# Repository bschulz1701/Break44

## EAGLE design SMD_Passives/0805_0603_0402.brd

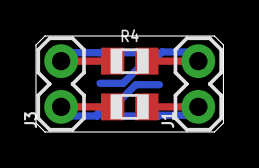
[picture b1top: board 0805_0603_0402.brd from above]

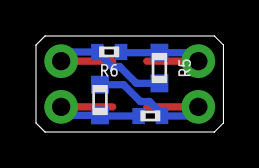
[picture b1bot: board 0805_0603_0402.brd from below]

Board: 2 copper layers, 10.4 x 5.3 mm, 8 parts (4 on the bottom side), 4 nets.

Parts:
J1, J3: 1X02
R1, R4: R0805
R2, R5: R0603
R3, R6: R0402

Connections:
R1_A: J3.1, R1.1, R2.1, R3.1
R1_B: J1.1, R1.2, R2.2, R3.2
R2_A: J3.2, R4.1, R5.1, R6.1
R2_B: J1.2, R4.2, R5.2, R6.2

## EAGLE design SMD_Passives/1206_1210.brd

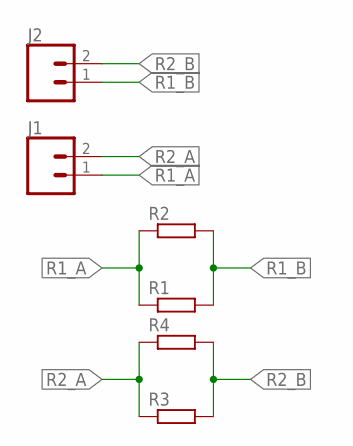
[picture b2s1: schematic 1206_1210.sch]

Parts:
J1, J2: CONN_02; 1X02
R1, R3: R-EU_R1210; R1210
R2, R4: R-EU_R1206; R1206

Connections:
R1_A: J1.1, R1.1, R2.1
R1_B: J2.1, R1.2, R2.2
R2_A: J1.2, R3.1, R4.1
R2_B: J2.2, R3.2, R4.2

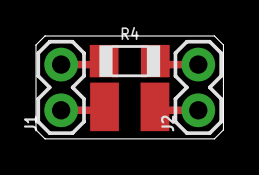
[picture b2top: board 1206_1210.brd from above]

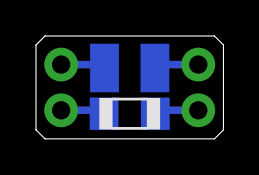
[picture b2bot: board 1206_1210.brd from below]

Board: 2 copper layers, 10.4 x 5.7 mm, 6 parts (2 on the bottom side), 4 nets.

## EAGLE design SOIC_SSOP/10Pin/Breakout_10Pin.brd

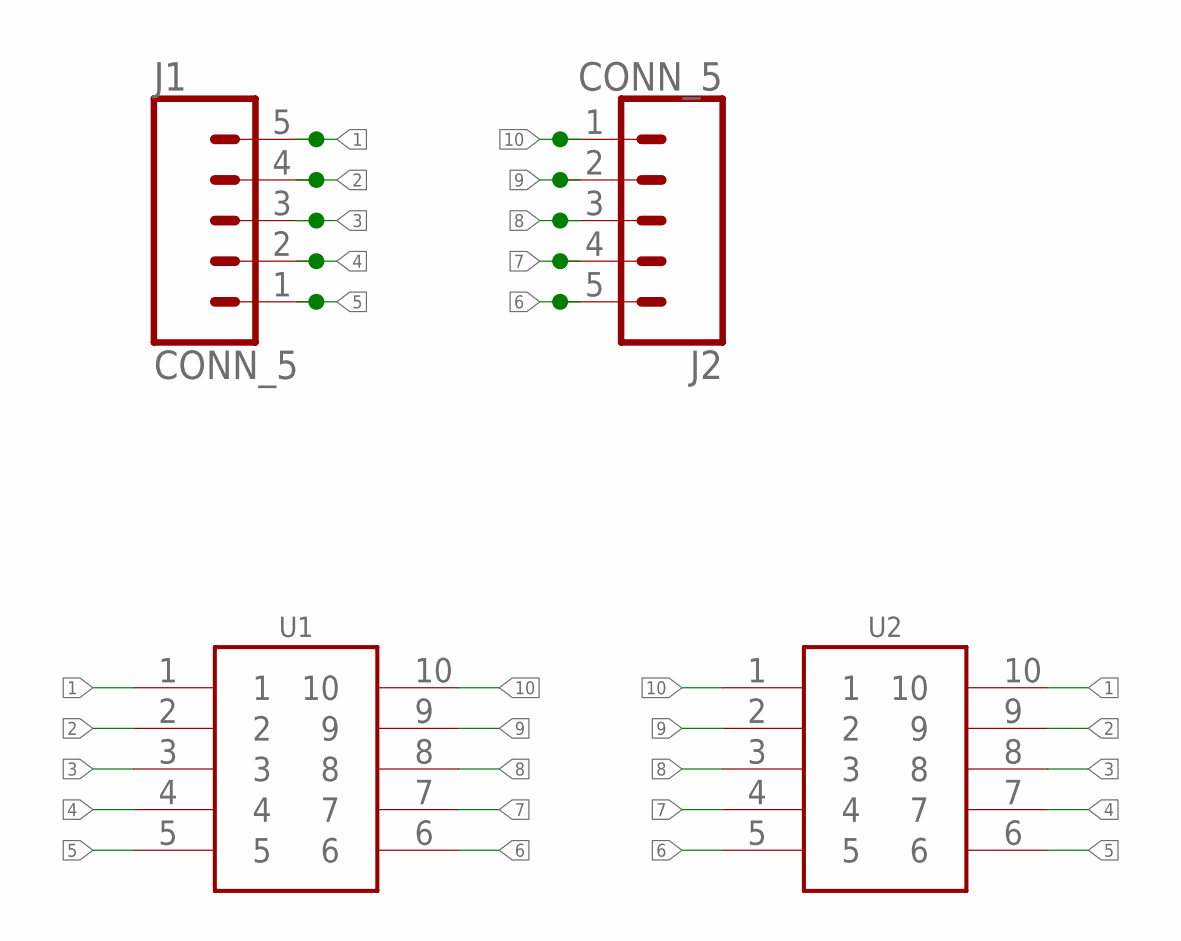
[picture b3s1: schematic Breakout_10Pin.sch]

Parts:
J1, J2: CONN_5; 1X05
U1: GEN_10SOIC10; SO10
U2: GEN_10VSSOP10; VSSOP_10

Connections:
1: J1.5, U1.1, U2.10
2: J1.4, U1.2, U2.9
3: J1.3, U1.3, U2.8
4: J1.2, U1.4, U2.7
5: J1.1, U1.5, U2.6
6: J2.5, U1.6, U2.5
7: J2.4, U1.7, U2.4
8: J2.3, U1.8, U2.3
9: J2.2, U1.9, U2.2
10: J2.1, U1.10, U2.1

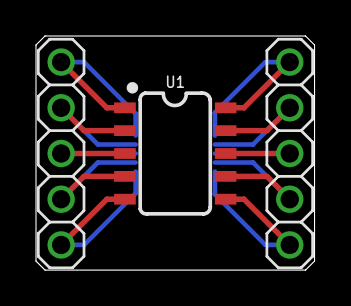
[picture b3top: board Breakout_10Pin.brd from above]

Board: 2 copper layers, 15.5 x 13.0 mm, 4 parts (1 on the bottom side), 10 nets.

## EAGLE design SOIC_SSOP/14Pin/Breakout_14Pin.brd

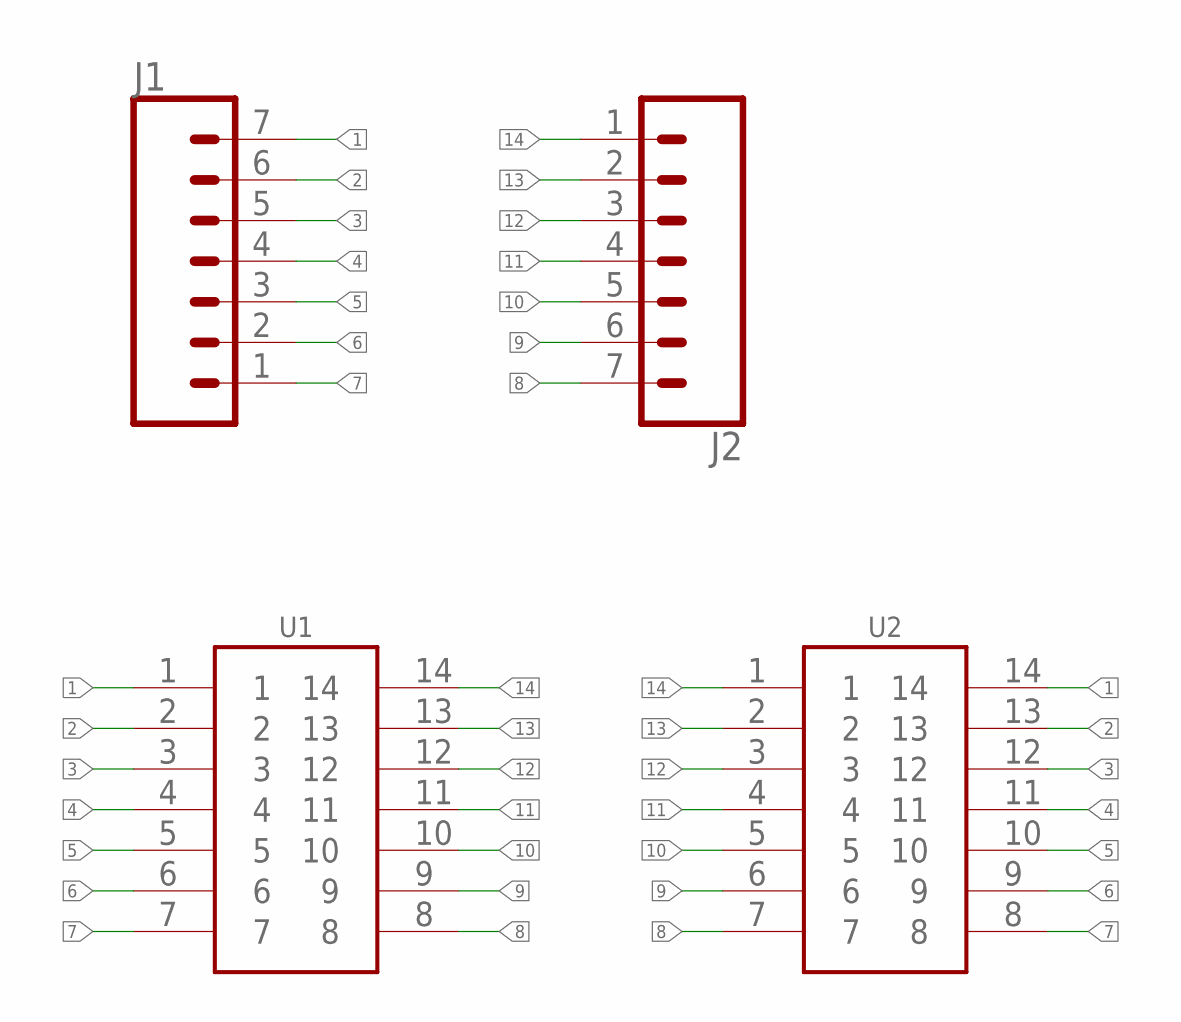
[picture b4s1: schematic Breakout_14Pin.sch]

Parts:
J1, J2: CONN_07; 1X07
U1: GEN_14SOIC; SO14
U2: GEN_14TSSOP; TSSOP14

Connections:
1: J1.7, U1.1, U2.14
2: J1.6, U1.2, U2.13
3: J1.5, U1.3, U2.12
4: J1.4, U1.4, U2.11
5: J1.3, U1.5, U2.10
6: J1.2, U1.6, U2.9
7: J1.1, U1.7, U2.8
8: J2.7, U1.8, U2.7
9: J2.6, U1.9, U2.6
10: J2.5, U1.10, U2.5
11: J2.4, U1.11, U2.4
12: J2.3, U1.12, U2.3
13: J2.2, U1.13, U2.2
14: J2.1, U1.14, U2.1

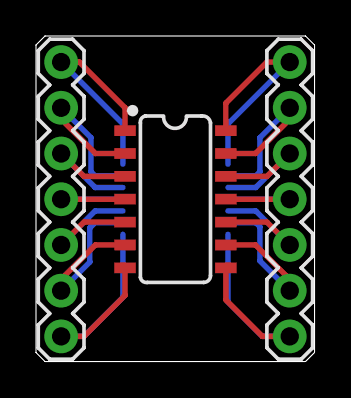
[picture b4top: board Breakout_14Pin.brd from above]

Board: 2 copper layers, 15.5 x 18.1 mm, 4 parts (1 on the bottom side), 14 nets.

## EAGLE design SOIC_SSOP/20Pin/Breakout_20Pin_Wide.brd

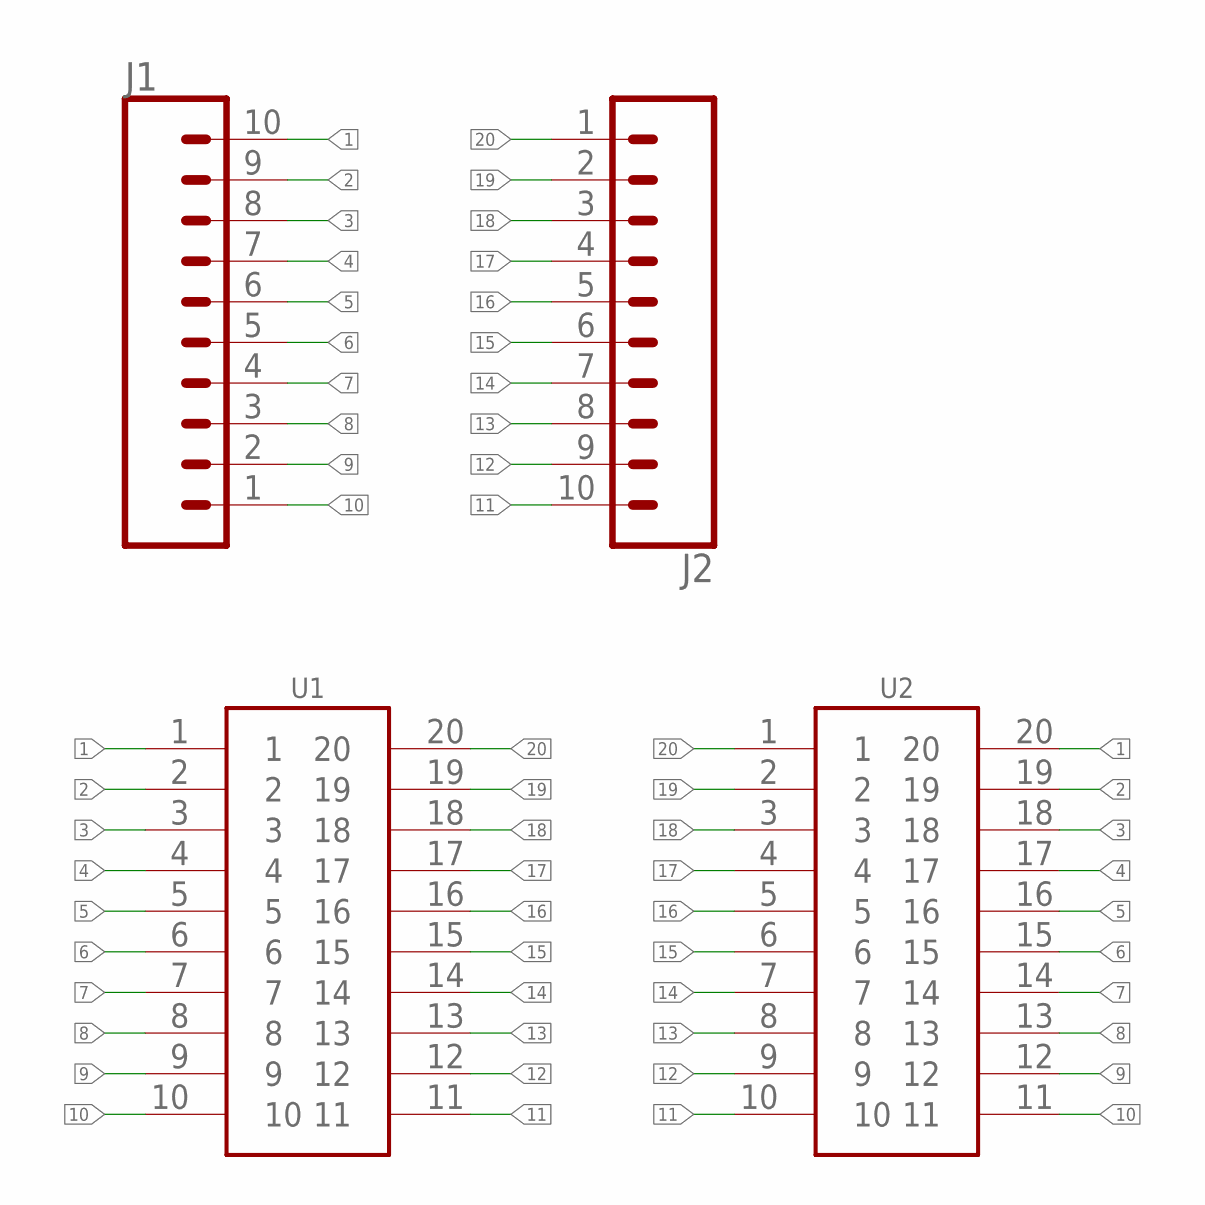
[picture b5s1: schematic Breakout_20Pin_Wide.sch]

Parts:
J1, J2: CONN_10"; 1X10
U1: GEN_20SOIC_W; SO-20DW
U2: GEN_20SSOP; SSOP20

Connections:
1: J1.10, U1.1, U2.20
2: J1.9, U1.2, U2.19
3: J1.8, U1.3, U2.18
4: J1.7, U1.4, U2.17
5: J1.6, U1.5, U2.16
6: J1.5, U1.6, U2.15
7: J1.4, U1.7, U2.14
8: J1.3, U1.8, U2.13
9: J1.2, U1.9, U2.12
10: J1.1, U1.10, U2.11
11: J2.10, U1.11, U2.10
12: J2.9, U1.12, U2.9
13: J2.8, U1.13, U2.8
14: J2.7, U1.14, U2.7
15: J2.6, U1.15, U2.6
16: J2.5, U1.16, U2.5
17: J2.4, U1.17, U2.4
18: J2.3, U1.18, U2.3
19: J2.2, U1.19, U2.2
20: J2.1, U1.20, U2.1

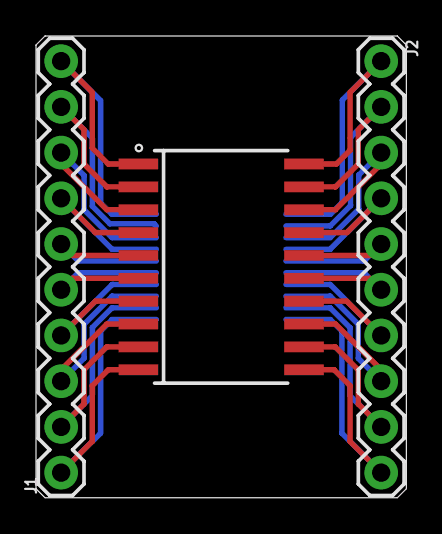
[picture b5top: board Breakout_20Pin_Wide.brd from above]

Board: 2 copper layers, 20.6 x 25.7 mm, 4 parts (1 on the bottom side), 20 nets.

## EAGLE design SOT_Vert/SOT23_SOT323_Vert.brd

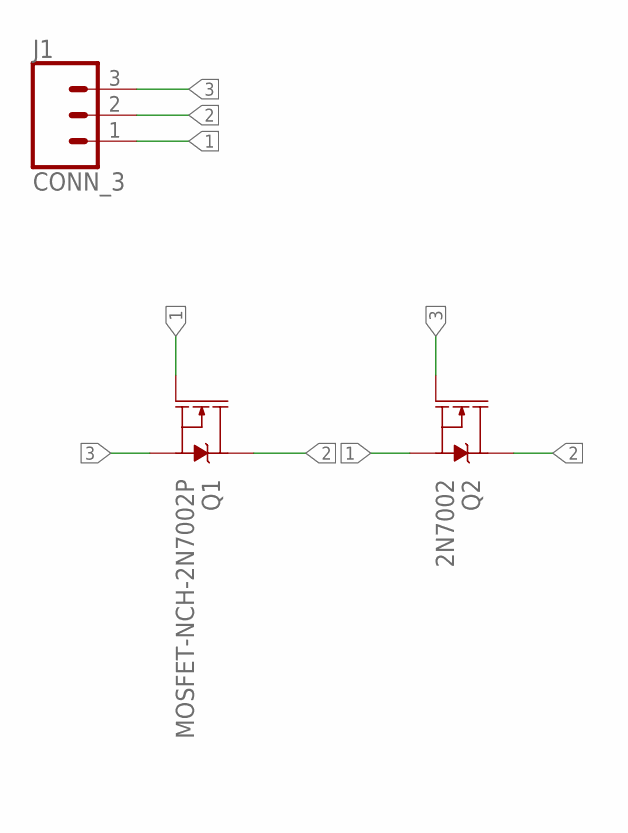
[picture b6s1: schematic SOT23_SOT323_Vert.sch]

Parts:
J1: CONN_3; 1X03
Q1: MOSFET-NCH-2N7002P; SOT23-3
Q2: 2N7002; SOT323

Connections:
1: J1.1, Q1.1 (G), Q2.2 (S)
2: J1.2, Q1.3 (D), Q2.3 (D)
3: J1.3, Q1.2 (S), Q2.1 (G)

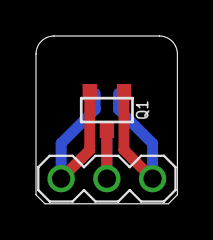
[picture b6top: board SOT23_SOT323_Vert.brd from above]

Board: 2 copper layers, 7.9 x 9.3 mm, 3 parts (1 on the bottom side), 3 nets.

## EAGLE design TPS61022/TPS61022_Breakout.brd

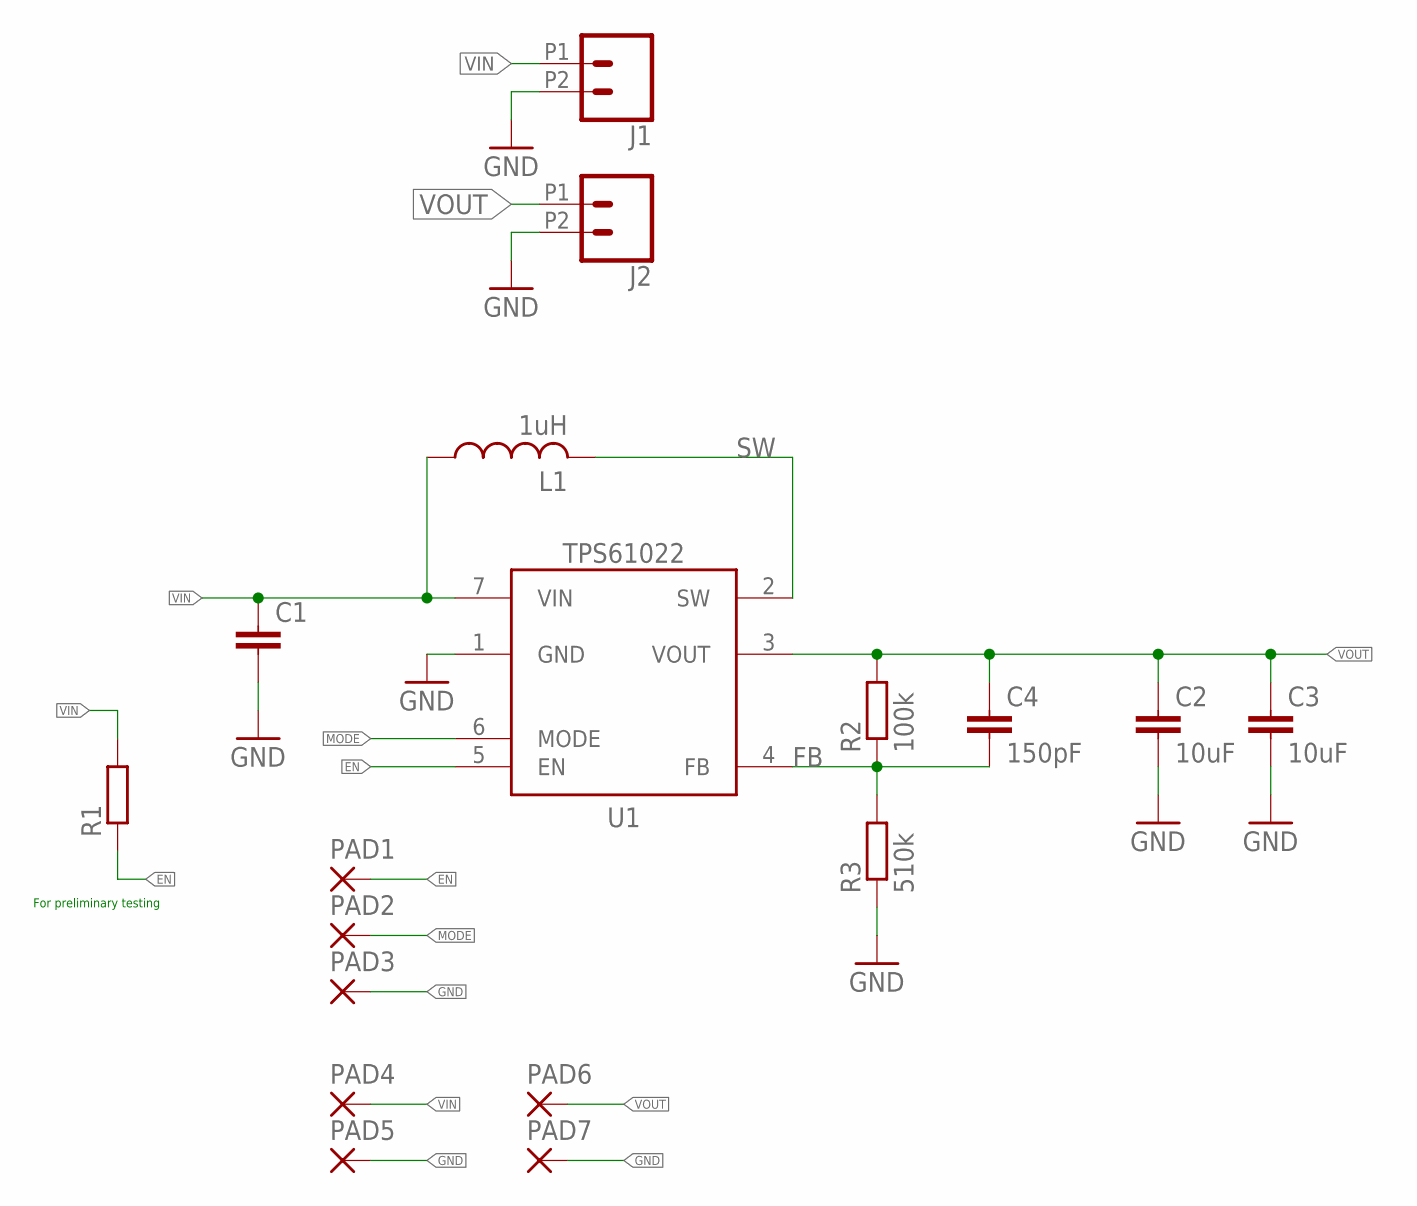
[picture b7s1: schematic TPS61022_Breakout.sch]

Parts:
C1: C-EUC0805; C0805
C2, C3: 10uF; C0805
C4: 150pF; C0603
J1, J2: CONN_022.54_SCREW_ROUND; 1X02_2.54_SCREWTERM_ROUND
L1: 1uH; WE-HCI(5040)
PAD1, PAD2, PAD3: SMD2; SMD1,27-2,54
PAD4, PAD5, PAD6, PAD7: SMD5; SMD2,54-5,08
R1: R-EU_100KR0603; R0603
R2: 100k; R0603
R3: 510k; R0603
U1: TPS61022; RWU0007A

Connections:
EN: PAD1.1, R1.1, U1.5 (EN)
FB: C4.2, R2.1, R3.2, U1.4 (FB)
GND: C1.2, C2.2, C3.2, J1.P2 (2), J2.P2 (2), PAD3.1, PAD5.1, PAD7.1, R3.1, U1.1 (GND)
MODE: PAD2.1, U1.6 (MODE)
SW: L1.P$2 (2), U1.2 (SW)
VIN: C1.1, J1.P1 (1), L1.P$1 (1), PAD4.1, R1.2, U1.7 (VIN)
VOUT: C2.1, C3.1, C4.1, J2.P1 (1), PAD6.1, R2.2, U1.3 (VOUT)

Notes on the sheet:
For preliminary testing

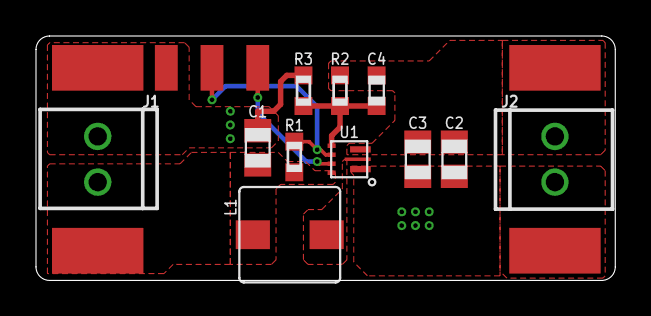
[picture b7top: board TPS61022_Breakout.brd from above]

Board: 2 copper layers, 32.2 x 13.6 mm, 18 parts (0 on the bottom side), 7 nets.
